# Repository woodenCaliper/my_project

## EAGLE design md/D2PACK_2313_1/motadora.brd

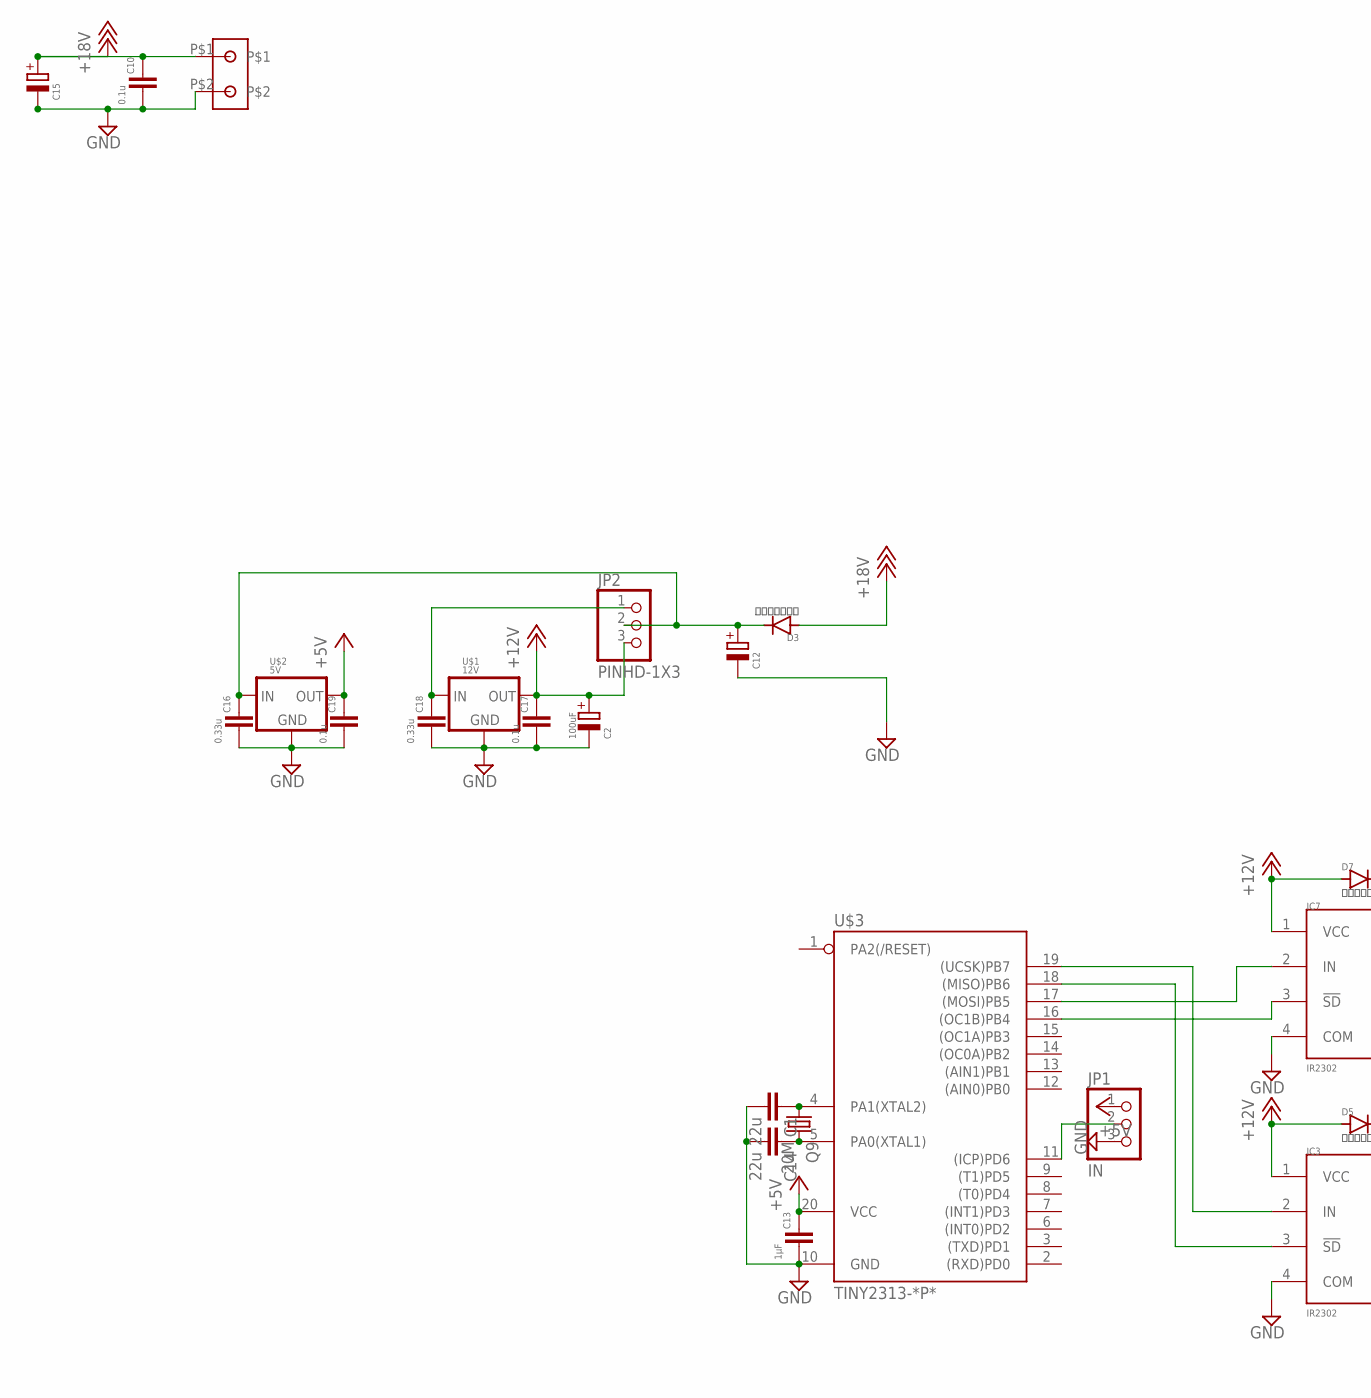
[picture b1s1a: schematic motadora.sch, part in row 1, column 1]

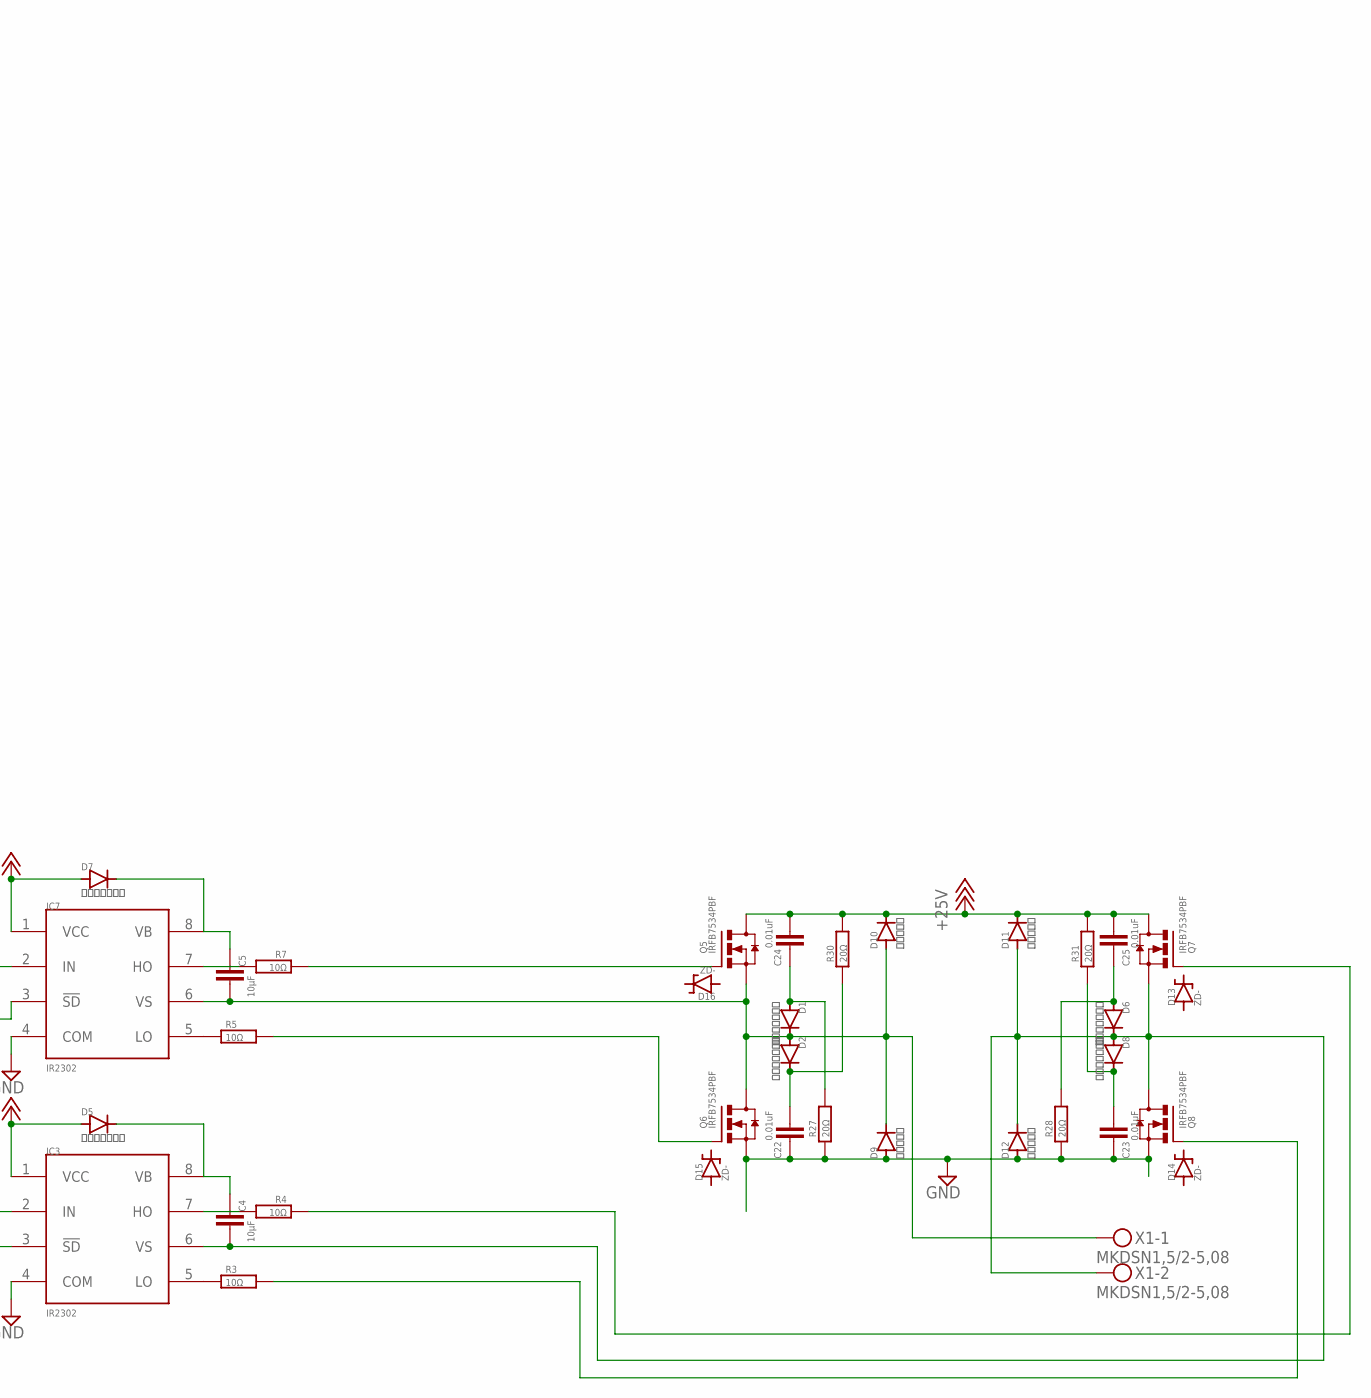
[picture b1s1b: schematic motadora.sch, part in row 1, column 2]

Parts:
C1, C14: 22u; C025-024X044
C2: 100uF; E2,5-7
C4, C5: 10μF; C050-024X044
C10, C17, C19: 0.1u; 2012
C12, C15: CPOL-EUE2.5-7; E2,5-7
C13: 1μF; C050-024X044
C16, C18: 0.33u; 2012
C22, C23, C24, C25: 0.01uF; 2012
D1, D2, D6, D8: １Ｎ４１４８Ｗ; SOD123
D3, D5, D7: １Ｎ４１４８Ｗ; D-7.5
D9, D10, D11, D12: ＭＳ１８Ｆ; ^MS18F
D13, D14, D15, D16: ZD-; ^U1ZB
IC3, IC7: IR2302; DIL08
JP1: IN; 1X03
JP2: PINHD-1X3; 1X03
Q5, Q6, Q7, Q8: IRFB7534PBF; D2PACK
Q9: 20M; HC49/S
R3, R4, R5, R7: 10Ω; 2012
R27, R28, R30, R31: 20Ω; 2012
T1: TANSIDAI; A
U$1: 12V; SOT-89
U$2: 5V; SOT-89
U$3: TINY2313-*P*; DIL20
X1: MKDSN1,5/2-5,08

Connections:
+5V: C13.1, C19.1, JP1.1, U$2.1 (OUT), U$3.20 (VCC)
+12V: C2.+, C17.1, D5.A, D7.A, IC3.1 (VCC), IC7.1 (VCC), JP2.3, U$1.1 (OUT)
+18V: C10.1, C15.+, C24.2, C25.2, D3.A, D10.CATHODE (C), D11.CATHODE (C), Q5.2 (D), Q7.2 (D), R30.2, R31.2, T1.P$1
GND: C1.2, C2.-, C10.2, C12.-, C13.2, C14.2, C15.-, C16.2, C17.2, C18.2, C19.2, C22.1, C23.1, D9.ANODE (A), D12.ANODE (A), IC3.4 (COM), IC7.4 (COM), JP1.3, Q6.3 (S), Q8.3 (S), R27.1, R28.1, T1.P$2, U$1.2 (GND), U$2.2 (GND), U$3.10 (GND)
unnamed: JP1.2, U$3.11 ((ICP)PD6)
unnamed: IC3.2 (IN), U$3.19 ((UCSK)PB7)
unnamed: IC7.2 (IN), U$3.17 ((MOSI)PB5)
unnamed: C5.2, D1.C, D2.A, D9.CATHODE (C), D10.ANODE (A), IC7.6 (VS), Q5.3 (S), Q6.2 (D), X1.1
unnamed: C24.1, D1.A, R27.2
unnamed: C22.2, D2.C, R30.1
unnamed: C14.1, Q9.2, U$3.5 (PA0(XTAL1))
unnamed: C1.1, Q9.1, U$3.4 (PA1(XTAL2))
unnamed: C23.2, D8.C, R31.1
unnamed: C25.1, D6.A, R28.2
unnamed: C18.1, JP2.1, U$1.3 (IN)
unnamed: Q8.1 (G), R3.2
unnamed: Q7.1 (G), R4.1
unnamed: IC3.5 (LO), R3.1
unnamed: IC3.3 (!SD), U$3.18 ((MISO)PB6)
unnamed: IC3.7 (HO), R4.2
unnamed: C4.1, D5.C, IC3.8 (VB)
unnamed: C4.2, D6.C, D8.A, D11.ANODE (A), D12.CATHODE (C), IC3.6 (VS), Q7.3 (S), Q8.2 (D), X1.2
unnamed: Q6.1 (G), R5.2
unnamed: Q5.1 (G), R7.1
unnamed: IC7.5 (LO), R5.1
unnamed: IC7.3 (!SD), U$3.16 ((OC1B)PB4)
unnamed: IC7.7 (HO), R7.2
unnamed: C5.1, D7.C, IC7.8 (VB)
unnamed: C12.+, C16.1, D3.C, JP2.2, U$2.3 (IN)

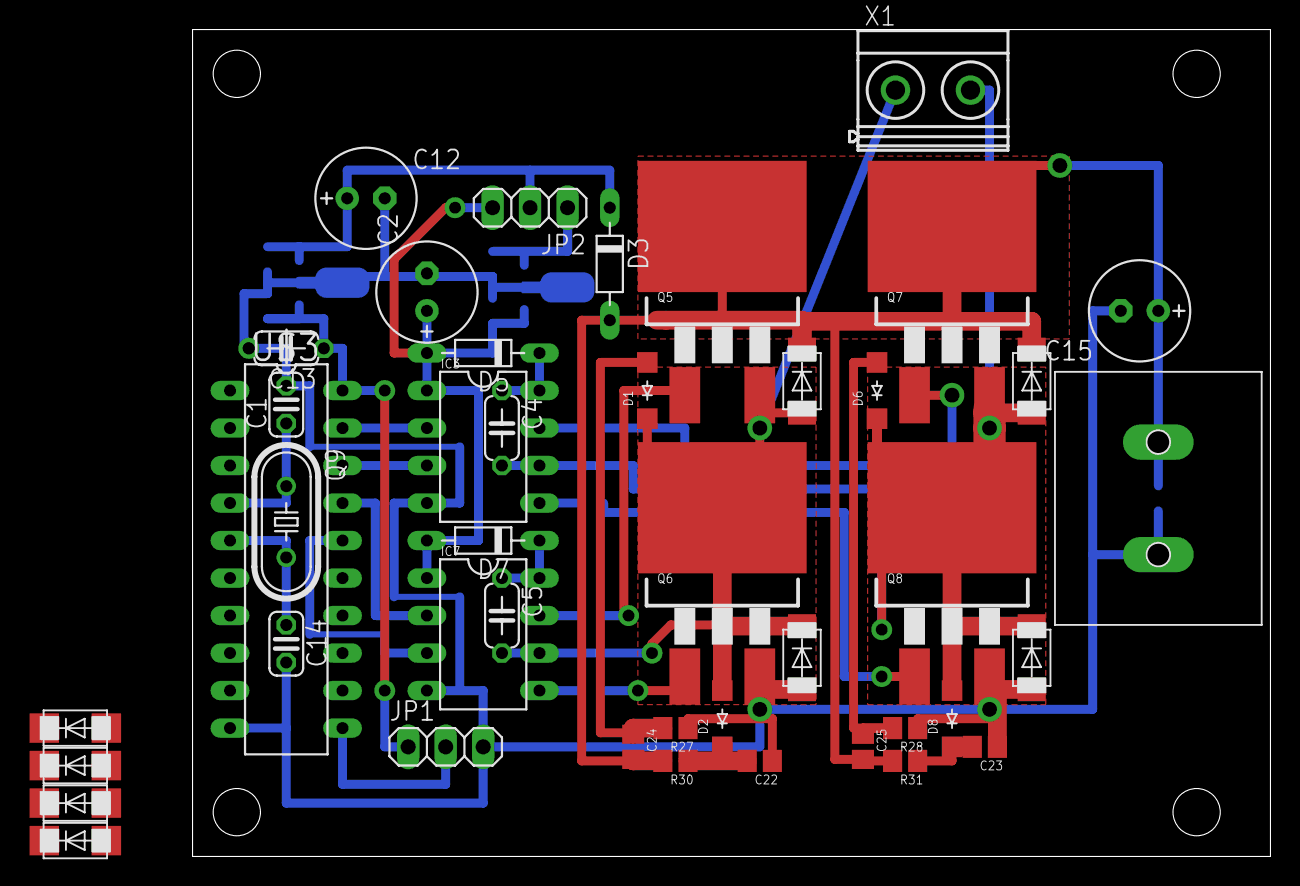
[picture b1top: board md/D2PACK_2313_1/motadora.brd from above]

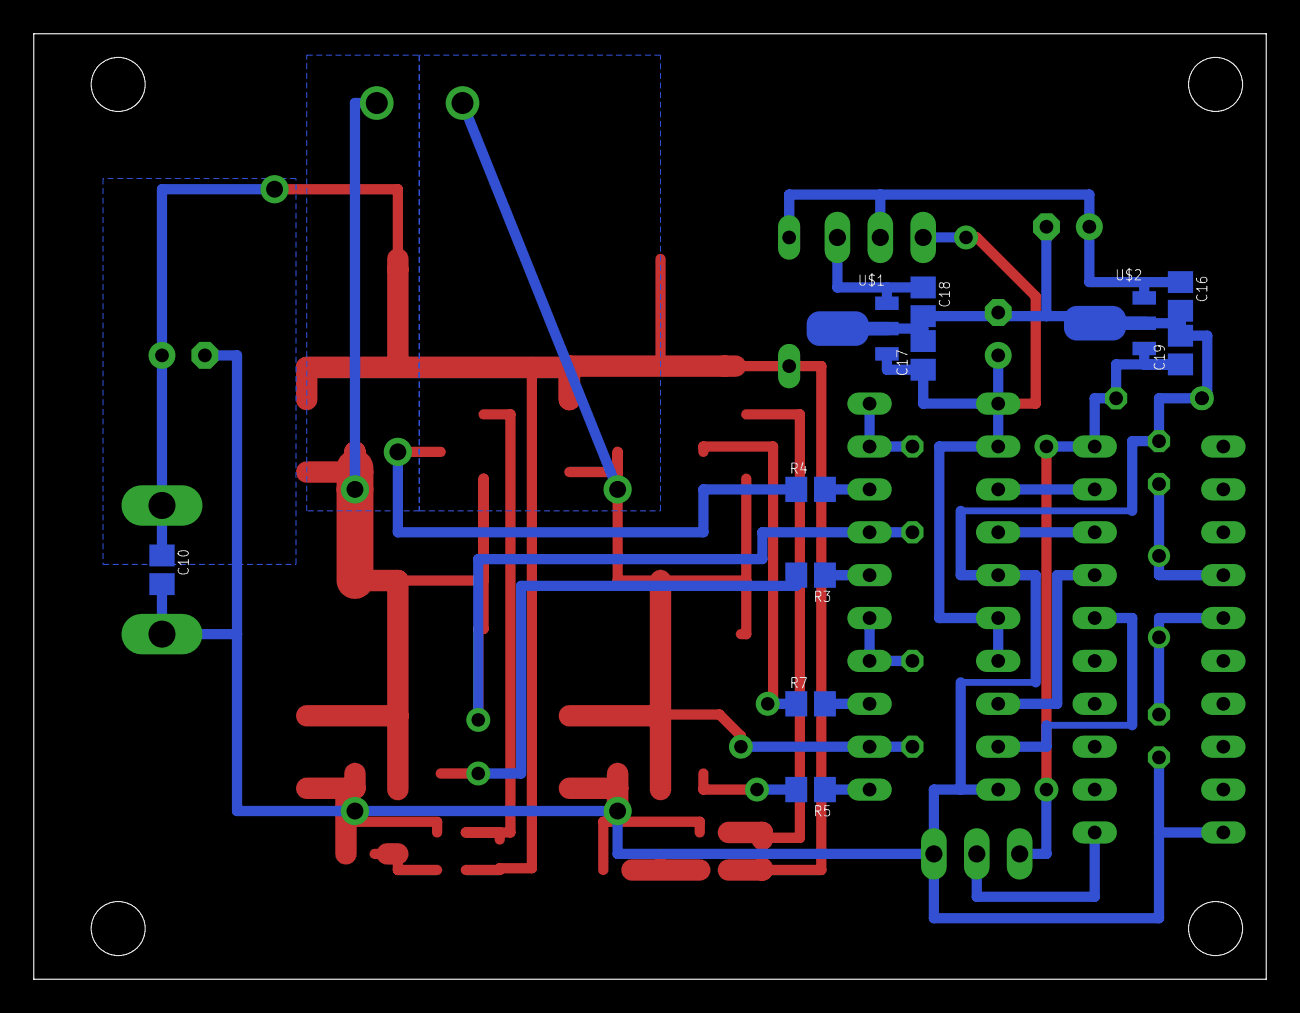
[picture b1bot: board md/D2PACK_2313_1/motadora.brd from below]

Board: 2 copper layers, 73.0 x 56.0 mm, 54 parts (11 on the bottom side), 29 nets.

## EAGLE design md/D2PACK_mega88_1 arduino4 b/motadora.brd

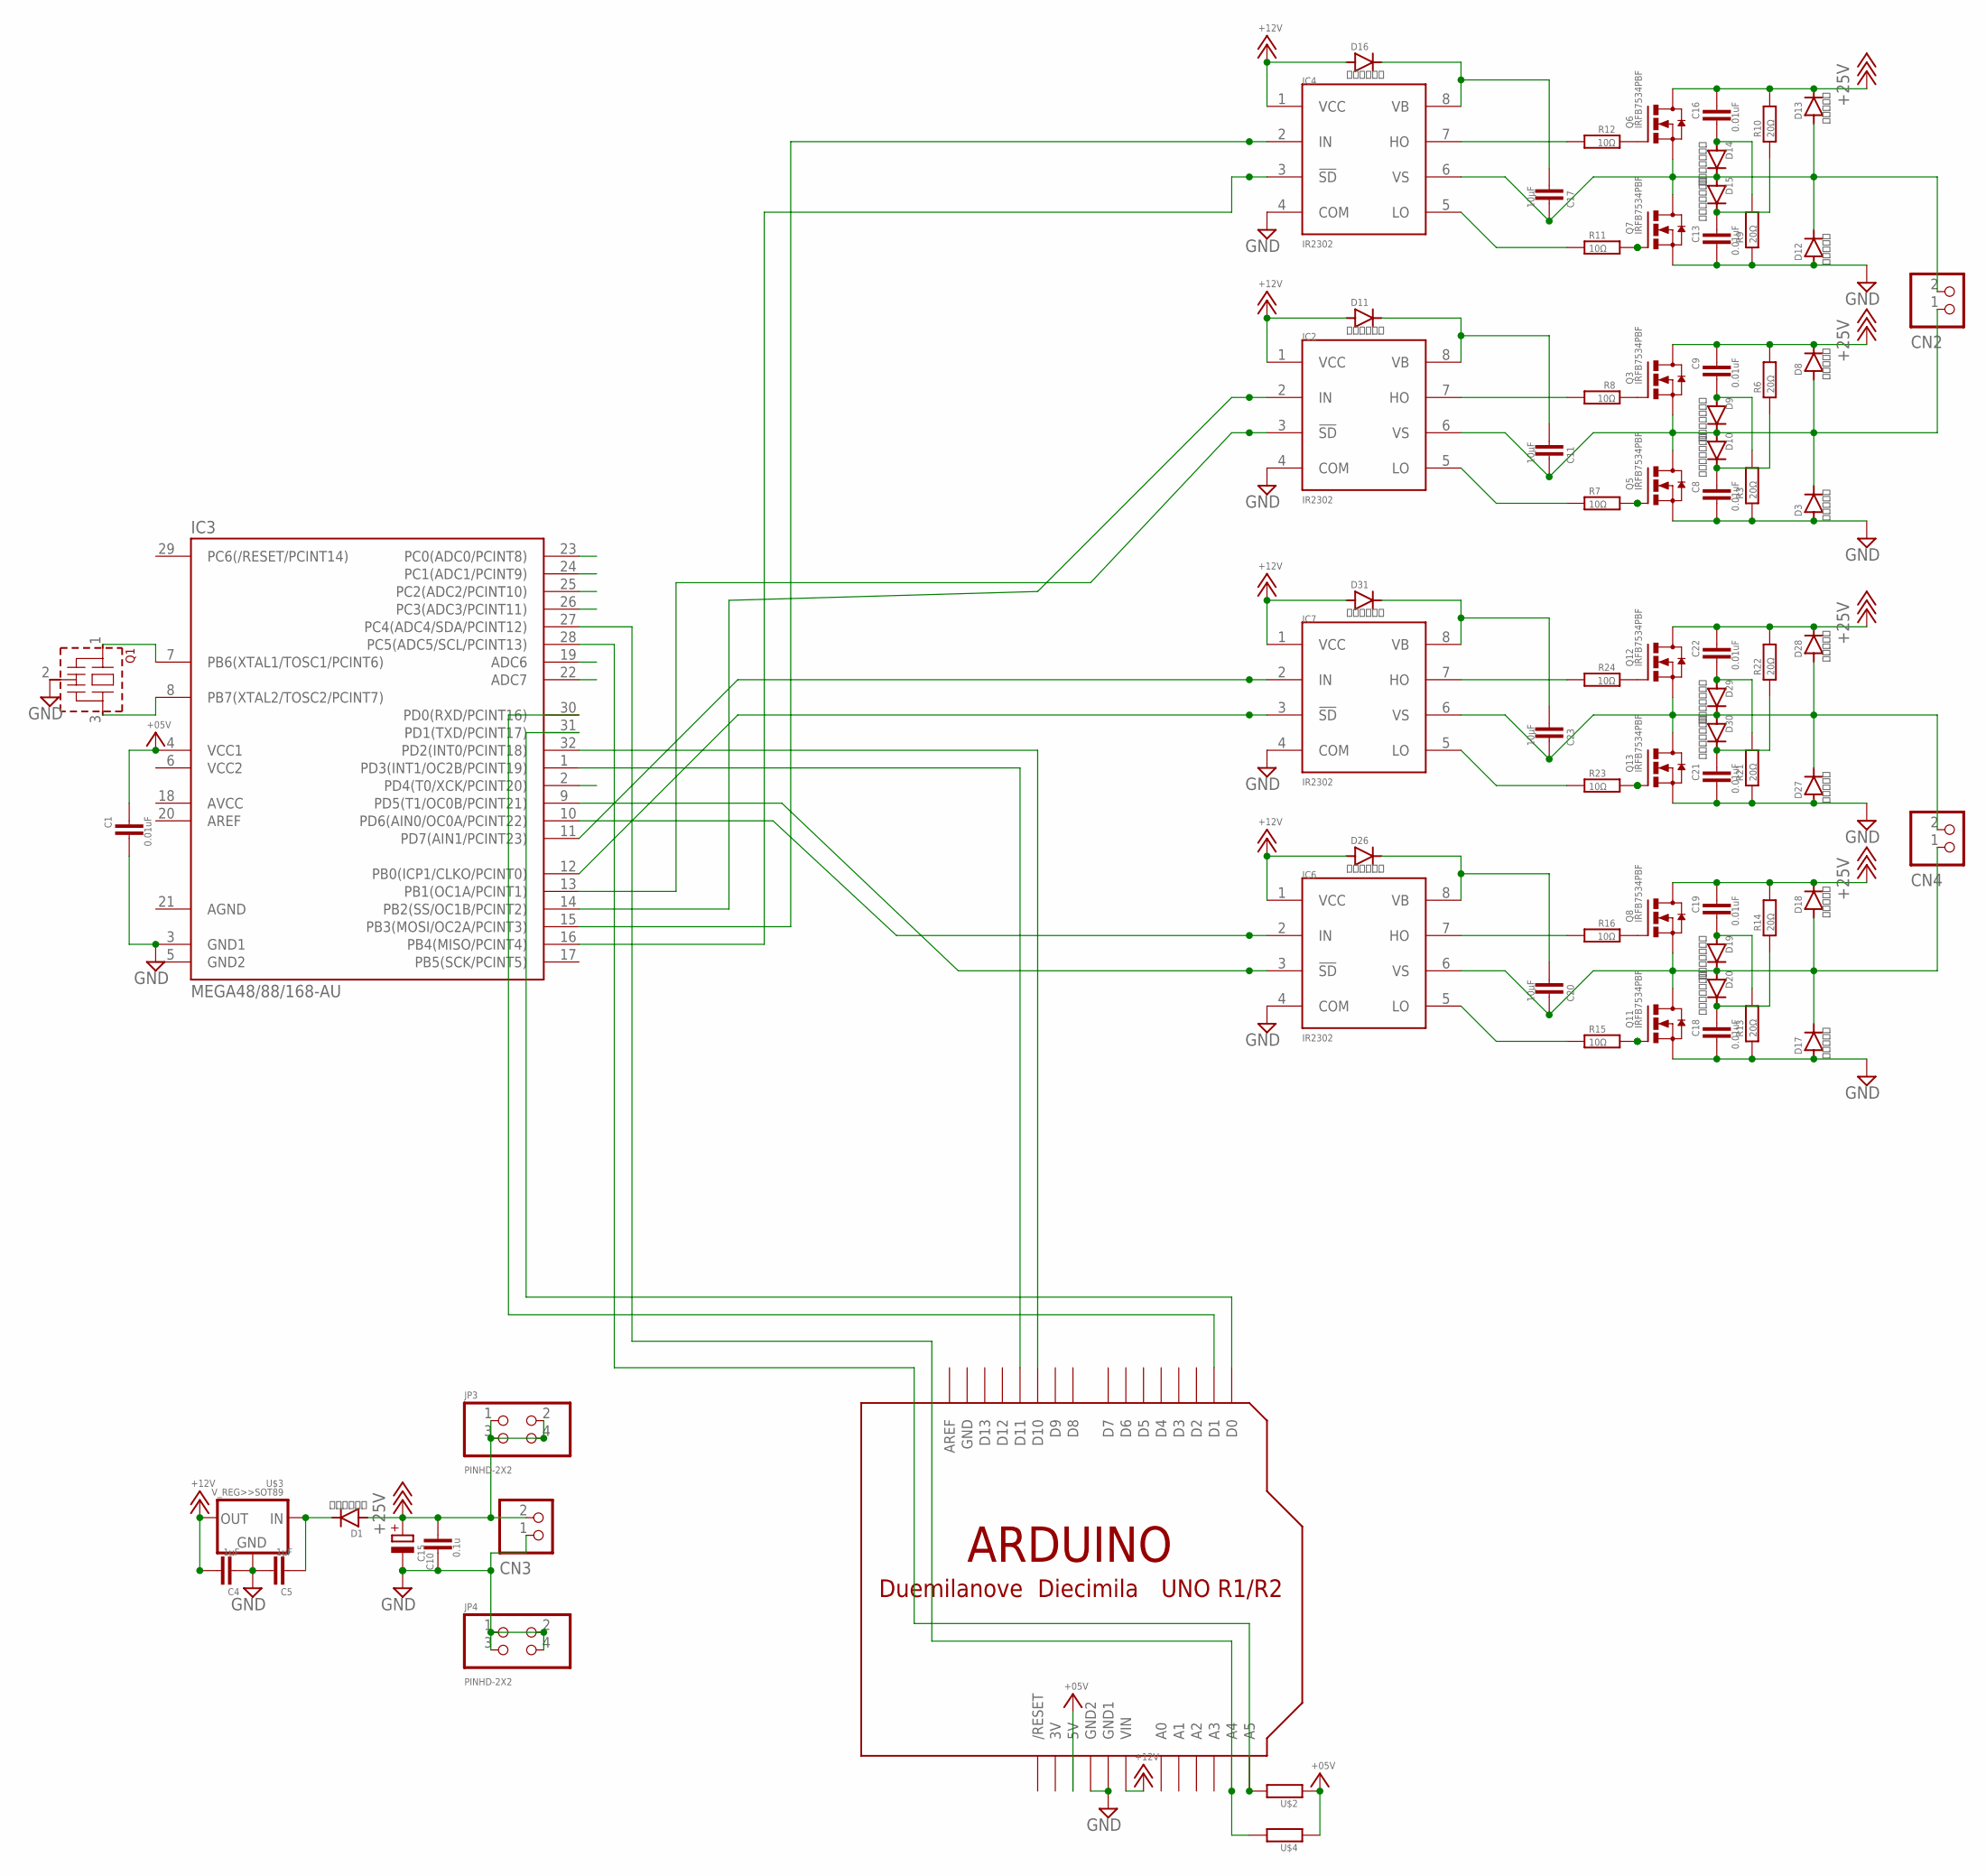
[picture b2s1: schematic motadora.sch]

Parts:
C1, C8, C9, C13, C16, C18, C19, C21, C22: 0.01uF; 2012
C4, C5: 1μF; 2012
C10: 0.1u; C025-025X050
C11, C17, C20, C23: 10μF; 2012
C15: CPOL-EUTT2D5L; TT2D5L
CN2, CN3, CN4: S2B-XH-A
D1: ＳＤ１０３Ａ; D-7.5
D3, D8, D12, D13, D17, D18, D27, D28: ＭＳ１８Ｆ; MS18F
D9, D10, D14, D15, D19, D20, D29, D30: １Ｎ４１４８Ｗ; SOD123
D11, D16, D26, D31: ＳＤ１０３Ａ; SOD123
IC2, IC4, IC6, IC7: IR2302; SO08
IC3: MEGA48/88/168-AU; TQFP32-08
JP3, JP4: PINHD-2X2; 2X02
Q1: CSTLS_G; CSTLS_G8
Q3, Q5, Q6, Q7, Q8, Q11, Q12, Q13: IRFB7534PBF; D2PACK
R3, R6, R9, R10, R13, R14, R21, R22: 20Ω; 2012
R7, R8, R11, R12, R15, R16, R23, R24: 10Ω; 2012
U$1: ARDUINO-NOHOLE
U$2, U$4: REGISTER>>2012; 2012
U$3: V_REG>>SOT89; SOT89

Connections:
3V: U$1.3V
+5V: C1.2, IC3.4 (VCC1), U$1.5V, U$2.1, U$4.1
+12V: C4.1, D11.A, D16.A, D26.A, D31.A, IC2.1 (VCC), IC4.1 (VCC), IC6.1 (VCC), IC7.1 (VCC), U$1.VIN, U$3.1 (OUT)
+18V: C9.2, C10.1, C15.+, C16.2, C19.2, C22.2, CN3.2, D1.A, D8.P$2 (C), D13.P$2 (C), D18.P$2 (C), D28.P$2 (C), JP3.1, JP3.2, JP3.3, JP3.4, Q3.2 (D), Q6.2 (D), Q8.2 (D), Q12.2 (D), R6.2, R10.2, R14.2, R22.2
AGND: IC3.21 (AGND)
GND: C1.1, C4.2, C5.1, C8.1, C10.2, C13.1, C15.-, C18.1, C21.1, CN3.1, D3.P$1 (A), D12.P$1 (A), D17.P$1 (A), D27.P$1 (A), IC2.4 (COM), IC3.3 (GND1), IC4.4 (COM), IC6.4 (COM), IC7.4 (COM), JP4.1, JP4.2, JP4.3, JP4.4, Q1.2 (VSS), Q5.3 (S), Q7.3 (S), Q11.3 (S), Q13.3 (S), R3.1, R9.1, R13.1, R21.1, U$1.GND, U$1.GND1, U$1.GND2, U$3.2 (GND), U$3.2.1 (GND)
GND2: IC3.5 (GND2)
unnamed: IC3.28 (PC5(ADC5/SCL/PCINT13)), U$1.A5, U$2.2
unnamed: IC3.27 (PC4(ADC4/SDA/PCINT12)), U$1.A4, U$4.2
unnamed: IC3.8 (PB7(XTAL2/TOSC2/PCINT7)), Q1.3
unnamed: IC3.31 (PD1(TXD/PCINT17)), U$1.D0
unnamed: IC3.30 (PD0(RXD/PCINT16)), U$1.D1
unnamed: IC3.32 (PD2(INT0/PCINT18)), U$1.D10
unnamed: C5.2, D1.C, U$3.3 (IN)
unnamed: IC3.1 (PD3(INT1/OC2B/PCINT19)), U$1.D11
unnamed: IC3.7 (PB6(XTAL1/TOSC1/PCINT6)), Q1.1
unnamed: IC2.2 (IN), IC3.14 (PB2(SS/OC1B/PCINT2))
unnamed: IC2.3 (!SD), IC3.13 (PB1(OC1A/PCINT1))
unnamed: C20.2, CN4.1, D17.P$2 (C), D18.P$1 (A), D19.C, D20.A, IC6.6 (VS), Q8.3 (S), Q11.2 (D)
unnamed: C19.1, D19.A, R13.2
unnamed: IC3.15 (PB3(MOSI/OC2A/PCINT3)), IC4.2 (IN)
unnamed: C18.2, D20.C, R14.1
unnamed: IC3.11 (PD7(AIN1/PCINT23)), IC7.2 (IN)
unnamed: Q11.1 (G), R15.2
unnamed: IC3.12 (PB0(ICP1/CLKO/PCINT0)), IC7.3 (!SD)
unnamed: C11.2, CN2.1, D3.P$2 (C), D8.P$1 (A), D9.C, D10.A, IC2.6 (VS), Q3.3 (S), Q5.2 (D)
unnamed: C9.1, D9.A, R3.2
unnamed: C8.2, D10.C, R6.1
unnamed: Q5.1 (G), R7.2
unnamed: IC2.5 (LO), R7.1
unnamed: IC2.7 (HO), R8.2
unnamed: C11.1, D11.C, IC2.8 (VB)
unnamed: IC3.16 (PB4(MISO/PCINT4)), IC4.3 (!SD)
unnamed: IC6.5 (LO), R15.1
unnamed: Q3.1 (G), R8.1
unnamed: IC6.7 (HO), R16.2
unnamed: C17.2, CN2.2, D12.P$2 (C), D13.P$1 (A), D14.C, D15.A, IC4.6 (VS), Q6.3 (S), Q7.2 (D)
unnamed: IC3.10 (PD6(AIN0/OC0A/PCINT22)), IC6.2 (IN)
unnamed: C16.1, D14.A, R9.2
unnamed: IC3.9 (PD5(T1/OC0B/PCINT21)), IC6.3 (!SD)
unnamed: C13.2, D15.C, R10.1
unnamed: Q7.1 (G), R11.2
unnamed: IC4.5 (LO), R11.1
unnamed: IC4.7 (HO), R12.2
unnamed: C17.1, D16.C, IC4.8 (VB)
unnamed: C20.1, D26.C, IC6.8 (VB)
unnamed: Q6.1 (G), R12.1
unnamed: Q8.1 (G), R16.1
unnamed: C23.2, CN4.2, D27.P$2 (C), D28.P$1 (A), D29.C, D30.A, IC7.6 (VS), Q12.3 (S), Q13.2 (D)
unnamed: C22.1, D29.A, R21.2
unnamed: C21.2, D30.C, R22.1
unnamed: Q13.1 (G), R23.2
unnamed: IC7.5 (LO), R23.1
unnamed: IC7.7 (HO), R24.2
unnamed: C23.1, D31.C, IC7.8 (VB)
unnamed: Q12.1 (G), R24.1
VCC2: IC3.6 (VCC2)

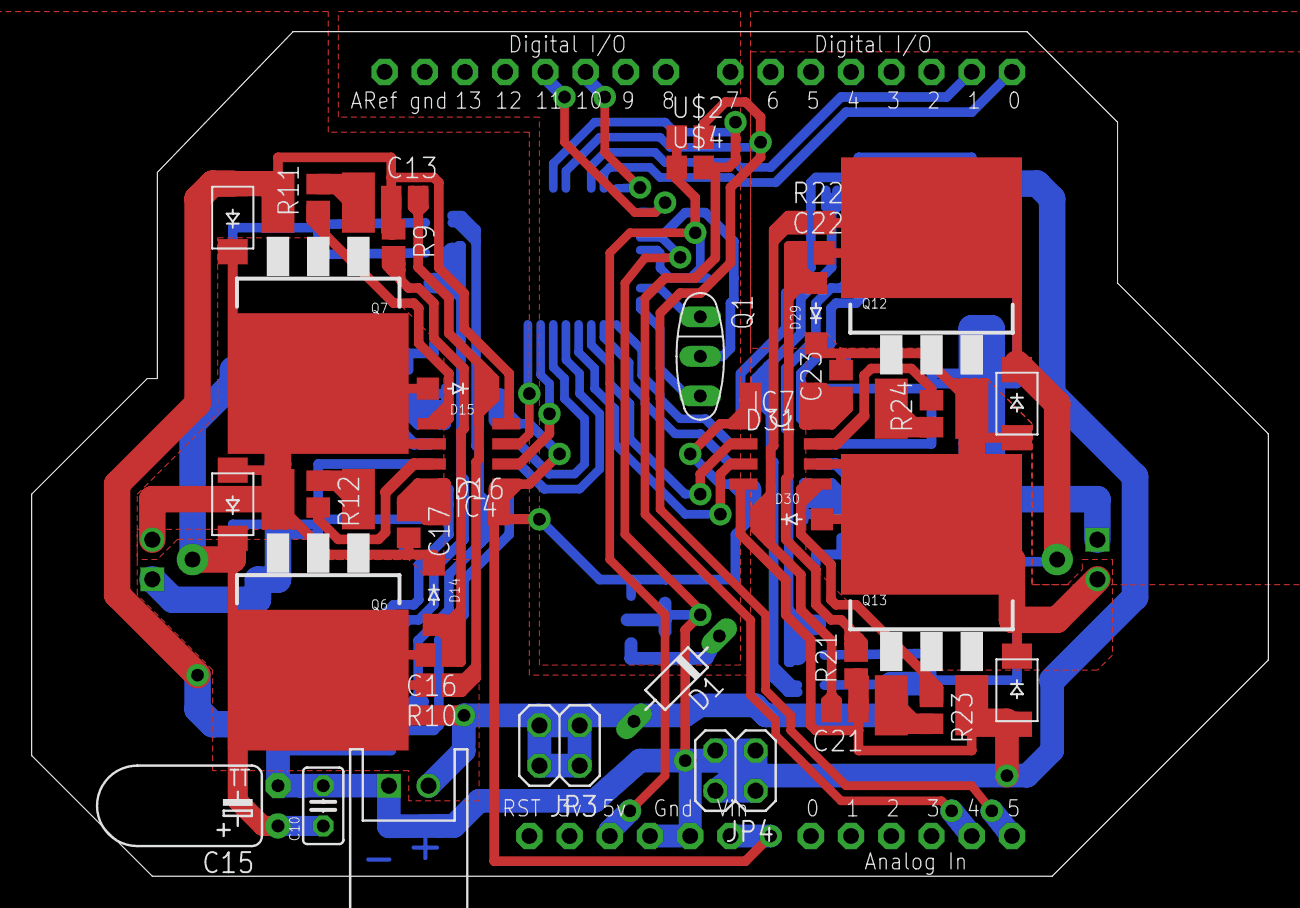
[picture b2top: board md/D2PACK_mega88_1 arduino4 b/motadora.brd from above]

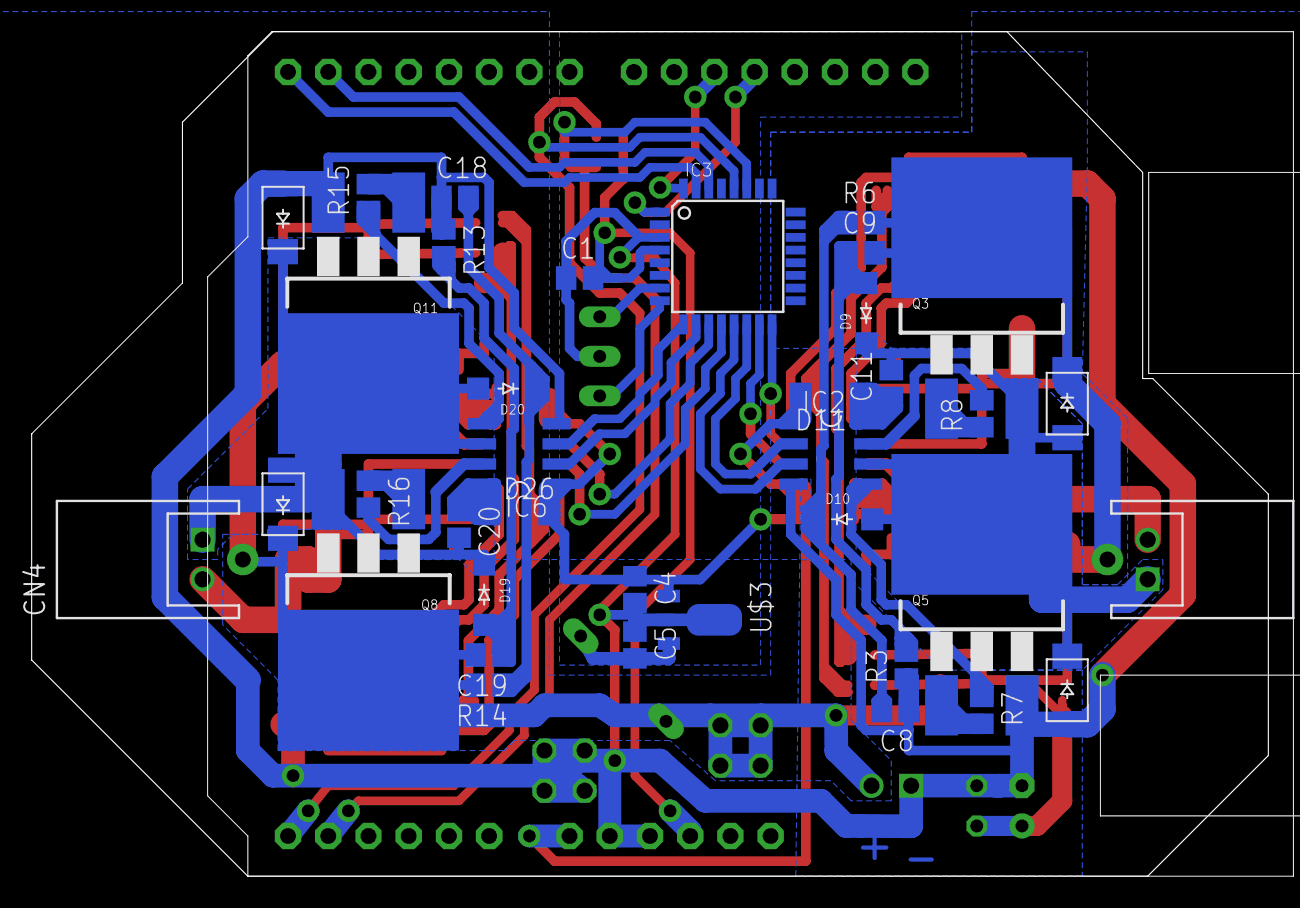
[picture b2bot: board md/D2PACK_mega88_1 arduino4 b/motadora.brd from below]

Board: 2 copper layers, 78.1 x 53.3 mm, 77 parts (37 on the bottom side), 53 nets.
